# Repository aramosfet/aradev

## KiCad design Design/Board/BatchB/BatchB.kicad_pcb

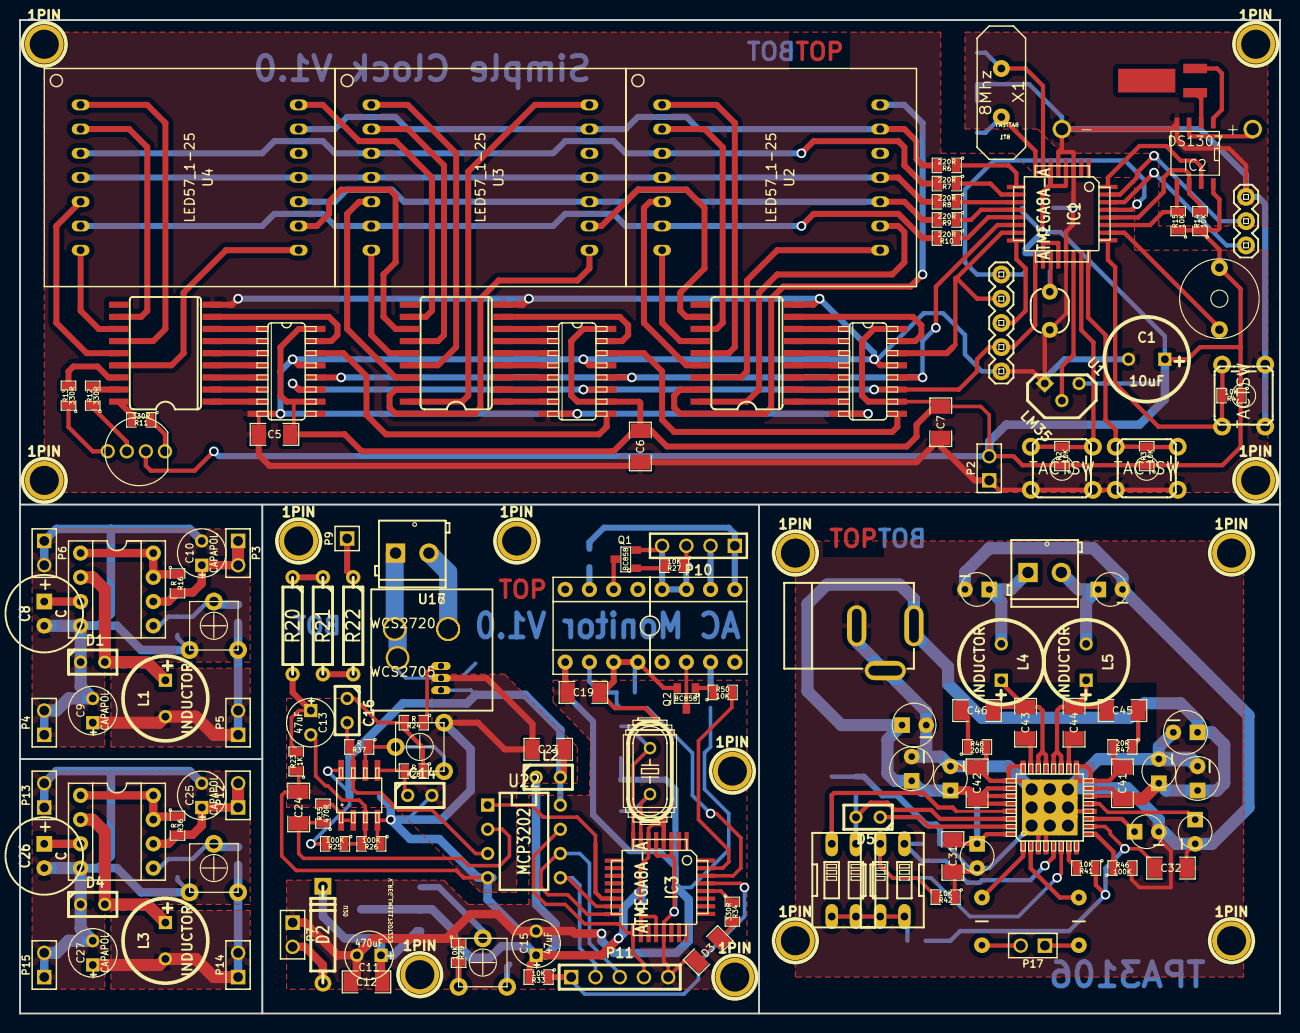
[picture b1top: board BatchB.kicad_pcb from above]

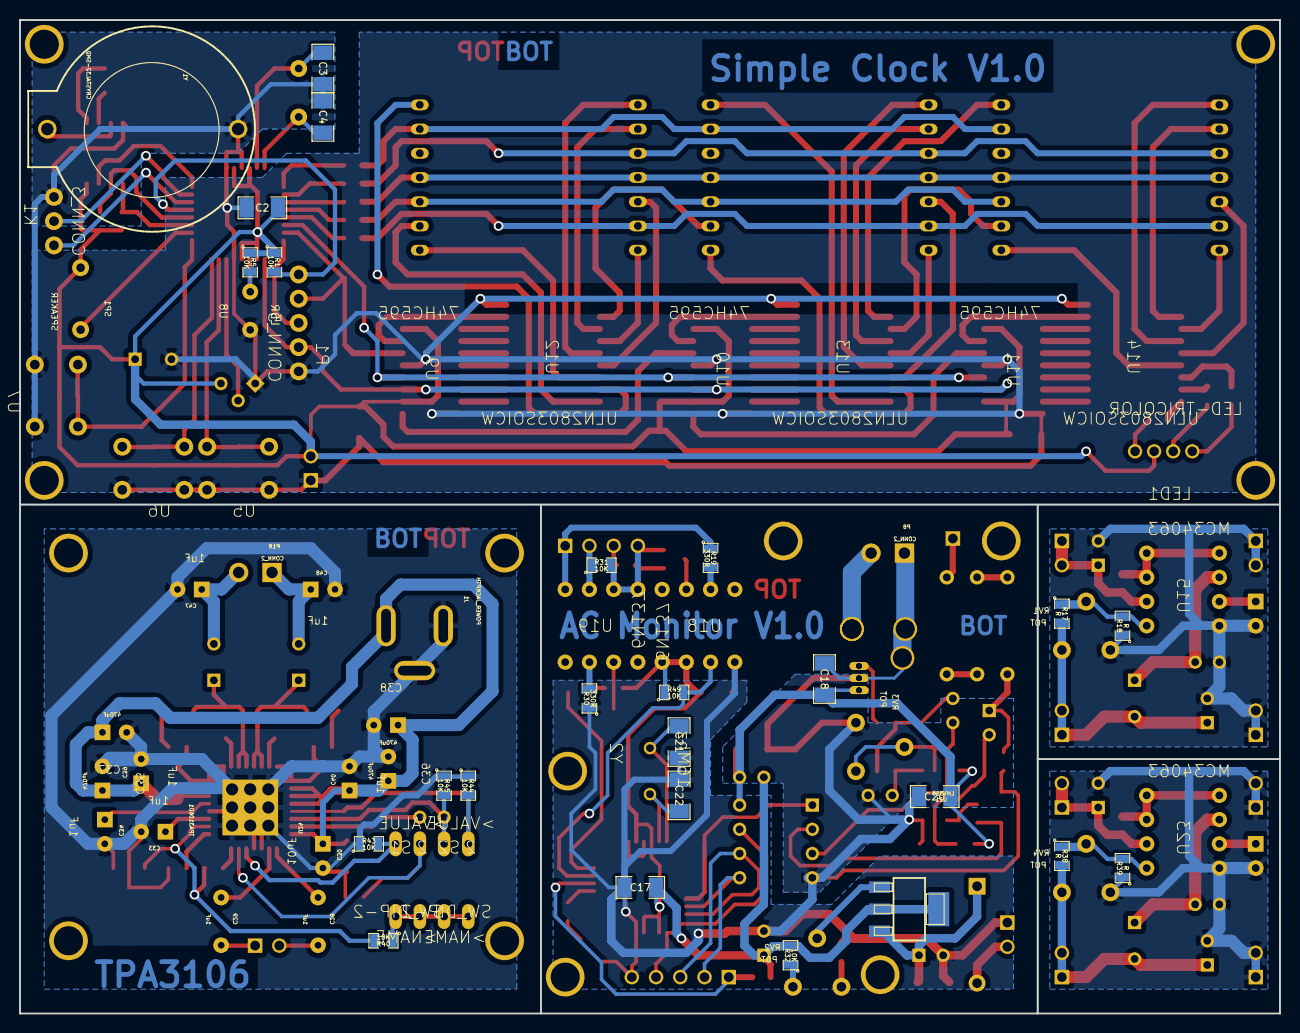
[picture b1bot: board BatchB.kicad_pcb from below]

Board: 4 copper layers, 132.1 x 104.1 mm, 181 parts (25 on the bottom side), 160 nets.

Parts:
1PIN, 1PIN#2, 1PIN#3, 1PIN#4, 1PIN#5, 1PIN#6, 1PIN#7, 1PIN#8, 1PIN#9, 1PIN#10, 1PIN#11, 1PIN#12, 1PIN#13: P***; 1pin
BT1: BATTERY; SparkFun-BATTCOM_20MM_PTH
C1: 10uF; C1.5V8V
C2, C5, C6, C7, C12, C17, C18, C19, C20, C23, C24, C31, C41, C42: 100nF; SM1206
C3, C4: 20pF; SM1206
C8, C26: C; C1V8
C9, C10, C25, C27: CAPAPOL; C1V5
C11: 470uF; C1V5
C13, C15: 47uF; C1V5
C14, C16: C; C1
C21, C22: 22pF; SM1206
C28, C29: 1uF; SparkFun-CAP-PTH-5MM
C30: 10uF; SparkFun-CPOL-RADIAL-10UF-25V
C32: 10nF; SM1206
C33, C34, C39, C40, C47, C48: 1uF; SparkFun-CPOL-RADIAL-10UF-25V
C35, C36, C37, C38: 470uF; SparkFun-CPOL-RADIAL-100UF-25V
C43, C44: 220nF; SM1206
C45, C46: 1nF; SM1206
D1, D4: DIODESCH; C1
D2: 1N4007; D4
D3: LED; SM1206
D5: DIODE; C1
IC1, IC3: ATMEGA8A-A; TQFP32
IC2: DS1307; SO8N
J1: POWER_JACKPTH; SparkFun-POWER_JACK_PTH
K1: CONN_3; SparkFun-1X03
L1, L3, L4, L5: INDUCTOR; C1.5V8V
L2: 100uH; C1
LED1: LED-TRICOLOR; LED-RGB-CA-PTH
P1: CONN_5; SparkFun-1X05
P2, P3, P4, P5, P6, P7, P12, P13, P14, P15, P17: CONN_2; PIN_ARRAY_2X1
P8, P18: CONN_2; SparkFun-SCREWTERMINAL-3.5MM-2
P9: CONN_1; PIN_ARRAY_1
P10: CONN_4; PIN_ARRAY_4x1
P11: CONN_5; PIN_ARRAY_5x1
Q1, Q2: BC858; SOT23
R1, R2, R3, R4, R5, R14, R15, R27, R29, R31, R32, R33, R40, R41, R42, R43, R44, R45, R49, R50: 10K; SM0805
R6, R7, R8, R9, R10: 220R; SM0805
R11, R12, R13, R19, R30, R34: 330R; SM0805
R16, R17, R18, R24, R28, R36, R37, R38, R39: R; SM0805
R20: 56K; R4
R21, R22: 470K; R4
R23: 1K; SM0805
R25, R26, R46: 100K; SM0805
R35: 470R; SM0805
R47, R48: 20R; SM0805
RV1, RV2, RV3, RV4: POT; SparkFun-TRIM_POT_PTH
S1, S2: SW_DIP-2; SparkFun-DIPSWITCH-02
SP1: SPEAKER; SparkFun-BUZZER-12MM
U1: LM35; TO92-123
U2, U3, U4: LED57_1-25
U5, U6, U7: TACTSW; SparkFun-TACTILE-PTH
U8: LDR; SparkFun-PHOTOCELL
U9, U10, U11: 74HC595; SparkFun-SO16
U12, U13, U14: ULN2803SOICW; SparkFun-SO18L
U15, U23: MC34063; SparkFun-DIL08
U16: WCS2705
U17: WCS2720
U18, U19: 6N137; SparkFun-DIL08
U20: V_REG_LM1117SOT223; SparkFun-SOT223
U21: LMV358; SparkFun-SOIC8
U22: MCP3202; DIP-8__300
U24: TPA3106D1; HLQFP33-PowerPAD
X1: 8Mhz; HC-18UV
Y1: CRYSTAL32-SMD; SparkFun-CRYSTAL-32KHZ-SMD
Y2: 16Mhz; SparkFun-HC49U-V

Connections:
/ClassDAmp/GAIN0: R43.2, S1.1, U24.5
/ClassDAmp/GAIN1: R42.2, S1.2, U24.6
/ClassDAmp/MUTE: D5.2, R45.2, S2.1, U24.30
/ClassDAmp/PVCC: C30.1, C31.1, C35.1, C36.1, C37.1, C38.1, C39.1, C40.1, C41.1, C42.1, J1.PWR, U24.14, U24.15, U24.26, U24.27, U24.28, U24.32
/ClassDAmp/SDZ: R44.2, S2.2, U24.29
/ClassDAmp/VREG: C32.1, R40.2, R41.1, U24.10
/EnergyADC/CS: IC3.14, U22.1
/EnergyADC/Iac: C16.2, R37.2, U21.7, U22.3
/EnergyADC/LED: IC3.28, R34.1
/EnergyADC/MISO: IC3.16, P11.3, U22.6
/EnergyADC/MOSI: IC3.15, P11.2, U22.5
/EnergyADC/RXD: IC3.30, R49.2, U18.6
/EnergyADC/Rst: IC3.29, P11.1, R33.1
/EnergyADC/SCK: IC3.17, P11.4, U22.7
/EnergyADC/TXD: IC3.31, R50.2
/EnergyADC/VCCA: C18.2, C20.2, C23.1, L2.2, R25.2, U16.Vdd, U17.Vdd, U21.8, U22.8
/EnergyADC/Vac: C24.2, R35.1, U22.2
/SimpleClock/Bt0: IC1.23, R2.2, U5.3, U5.4
/SimpleClock/Bt1: IC1.24, R3.2, U6.3, U6.4
/SimpleClock/Bt2: IC1.25, R4.2, U7.3, U7.4
/SimpleClock/Buz: IC1.26, SP1.2
/SimpleClock/CS: IC1.14, U9.12, U10.12, U11.12
/SimpleClock/Dc1: R6.2, U2.13, U3.13, U4.13
/SimpleClock/Dc2: R7.2, U2.3, U3.3, U4.3
/SimpleClock/Dc3: R8.2, U2.4, U2.11, U3.4, U3.11, U4.4, U4.11
/SimpleClock/Dc4: R9.2, U2.10, U3.10, U4.10
/SimpleClock/Dc5: R10.2, U2.6, U3.6, U4.6
/SimpleClock/Dr11: U2.9, U12.18
/SimpleClock/Dr12: U2.14, U12.17
/SimpleClock/Dr13: U2.8, U12.16
/SimpleClock/Dr14: U2.5, U12.15
/SimpleClock/Dr15: U2.1, U12.14
/SimpleClock/Dr16: U2.7, U12.13
/SimpleClock/Dr17: U2.2, U12.12
/SimpleClock/Dr21: U3.9, U12.11
/SimpleClock/Dr22: U3.14, U13.18
/SimpleClock/Dr23: U3.8, U13.17
/SimpleClock/Dr24: U3.5, U13.16
/SimpleClock/Dr25: U3.1, U13.15
/SimpleClock/Dr26: U3.7, U13.14
/SimpleClock/Dr27: U3.2, U13.13
/SimpleClock/Dr31: U4.9, U13.12
/SimpleClock/Dr32: U4.14, U13.11
/SimpleClock/Dr33: U4.8, U14.15
/SimpleClock/Dr34: U4.5, U14.14
/SimpleClock/Dr35: U4.1, U14.13
/SimpleClock/Dr36: U4.7, U14.12
/SimpleClock/Dr37: U4.2, U14.11
/SimpleClock/INT: IC1.32, IC2.7
/SimpleClock/LDR: IC1.19, R5.2, U8.1
/SimpleClock/LEDB: R13.2, U14.16
/SimpleClock/LEDG: R12.2, U14.17
/SimpleClock/LEDR: R11.2, U14.18
/SimpleClock/MISO: IC1.16, P1.3
/SimpleClock/MOSI: IC1.15, P1.4, U9.14
/SimpleClock/Qb1: U9.7, U12.1
/SimpleClock/Qb2: U9.6, U12.2
/SimpleClock/Qb3: U9.5, U12.3
/SimpleClock/Qb4: U9.4, U12.4
/SimpleClock/Qb5: U9.3, U12.5
/SimpleClock/Qb6: U9.2, U12.6
/SimpleClock/Qb7: U9.1, U12.7
/SimpleClock/Qb8: U9.15, U12.8
/SimpleClock/Qb9: U10.7, U13.1
/SimpleClock/Qb10: U10.6, U13.2
/SimpleClock/Qb11: U10.5, U13.3
/SimpleClock/Qb12: U10.4, U13.4
/SimpleClock/Qb13: U10.3, U13.5
/SimpleClock/Qb14: U10.2, U13.6
/SimpleClock/Qb15: U10.1, U13.7
/SimpleClock/Qb16: U10.15, U13.8
/SimpleClock/Qb17: U11.7, U14.1
/SimpleClock/Qb18: U11.6, U14.2
/SimpleClock/Qb19: U11.5, U14.3
/SimpleClock/Qb20: U11.4, U14.4
/SimpleClock/Qb21: U11.3, U14.5
/SimpleClock/Qb22: U11.2, U14.6
/SimpleClock/Qb23: U11.1, U14.7
/SimpleClock/Qb24: U11.15, U14.8
/SimpleClock/RST: IC1.29, P1.5, R1.2
/SimpleClock/RXD: IC1.30, K1.3
/SimpleClock/SCK: IC1.17, P1.2, U9.11, U10.11, U11.11
/SimpleClock/SCL: IC1.28, IC2.6, R14.2
/SimpleClock/SDA: IC1.27, IC2.5, R15.2
/SimpleClock/TXD: IC1.31, K1.2
/SimpleClock/Temp: IC1.22, U1.2
GND: BT1.2, C1.2, C2.2, C3.2, C4.2, C5.2, C6.2, C7.2, C8.2, C9.2, C10.2, C11.2, C12.1, C14.2, C15.2, C17.1, C18.1, C19.1, C20.1, C21.1, C22.1, C23.2, C24.1, C25.2, C26.2, C27.2, C30.2, C31.2, C32.2, C33.2, C34.2, C35.2, C36.2, C37.2, C38.2, C39.2, C40.2, C41.2, C42.2, C47.2, C48.2, D1.1, D3.2, D4.1, IC1.3, IC1.5, IC1.21, IC2.4, IC3.3, IC3.5, IC3.21, J1.GND, J1.GNDB, K1.1, P1.1, P2.1, P4.1, P4.2, P6.1, P6.2, P7.1, P8.1, P11.5, P13.1, P13.2, P15.1, P15.2, R18.1, R23.1, R26.1, R29.1, R30.1, R39.1, R42.1, R43.1, R44.1, R45.1, R46.2, R47.2, R48.2, RV1.1, RV3.3, RV4.1, U1.3, U5.1, U5.2, U6.1, U6.2, U7.1, U7.2, U8.2, U9.8, U9.13, U10.8, U10.13, U11.8, U11.13, U12.9, U13.9, U14.9, U15.4, U16.Gnd, U16.IP-, U17.Gnd, U17.IP-, U18.5, U21.4, U22.4, U23.4, U24.3, U24.4, U24.12, U24.16, U24.17, U24.24, U24.25, U24.33
unnamed: IC1.9, R6.1
unnamed: IC1.11, R8.1
unnamed: IC1.12, R9.1
unnamed: IC1.13, R10.1
unnamed: IC1.10, R7.1
unnamed: BT1.1, IC2.3
unnamed: IC2.1, Y1.2
unnamed: IC2.2, Y1.1
unnamed: LED1.B, R12.1
unnamed: LED1.G, R13.1
unnamed: LED1.R, R11.1
unnamed: C3.1, IC1.7, X1.1
unnamed: C4.1, IC1.8, X1.2
unnamed: U10.9, U11.14
unnamed: U9.9, U10.14
unnamed: C26.1, U23.3
unnamed: R36.1, U23.1, U23.7, U23.8
unnamed: D4.2, L3.1, U23.2
unnamed: C27.1, L3.2, P14.1, P14.2, R38.2, RV4.3
unnamed: R38.1, R39.2, RV4.2, U23.5
unnamed: C8.1, U15.3
unnamed: R16.1, U15.1, U15.7, U15.8
unnamed: D1.2, L1.1, U15.2
unnamed: C9.1, L1.2, P5.1, P5.2, R17.2, RV1.3
unnamed: R17.1, R18.2, RV1.2, U15.5
unnamed: D2.1, P7.2
unnamed: C14.1, R28.2, U21.5
unnamed: R35.2, U21.1, U21.2
unnamed: R32.1, RV2.3
unnamed: R29.2, RV2.1
unnamed: RV2.2, U20.1
unnamed: C11.1, C12.2, D2.2, U20.3
unnamed: C16.1, R24.2, R28.1
unnamed: P10.3, R27.1
unnamed: Q1.1, R27.2
unnamed: Q2.1, R50.1
unnamed: R30.2, U19.3
unnamed: Q1.3, U18.2
unnamed: R19.2, U18.3
unnamed: P9.1, R22.1
unnamed: C21.2, IC3.8, Y2.1
unnamed: R37.1, RV3.1, RV3.2, U21.6
unnamed: Q2.3, U19.2
unnamed: P10.1, R19.1, U19.5
unnamed: P10.2, R31.1, U19.6
unnamed: C13.2, R25.1, R26.2, U21.3
unnamed: C13.1, R20.2, R23.2
unnamed: R20.1, R21.1
unnamed: R21.2, R22.2
unnamed: C22.2, IC3.7, Y2.2
unnamed: P8.2, U16.IP+, U17.IP+
unnamed: R24.1, U16.Vo, U17.Vo
unnamed: D3.1, R34.2
unnamed: P10.4, Q1.2, R31.2, U19.7, U19.8
unnamed: C29.1, P17.1
unnamed: C28.1, P17.2
unnamed: D5.1, U24.31
unnamed: C29.2, U24.2
unnamed: C28.2, U24.1
unnamed: C46.1, R48.1
unnamed: C45.1, R47.1
unnamed: R40.1, S1.3, S1.4, S2.3, S2.4
unnamed: C43.2, C46.2, L4.1, U24.21, U24.22
unnamed: C44.1, U24.18
unnamed: C43.1, U24.23
unnamed: R46.1, U24.9
unnamed: C33.1, U24.11
unnamed: C44.2, C45.2, L5.1, U24.19, U24.20
unnamed: C47.1, L5.2, P18.2
unnamed: C48.1, L4.2, P18.1
unnamed: R41.2, U24.7
unnamed: C34.1, U24.13
VCC: C1.1, C2.1, C5.1, C6.1, C7.1, C10.1, C15.1, C17.2, C19.2, C25.1, IC1.4, IC1.6, IC1.18, IC1.20, IC2.8, IC3.4, IC3.6, IC3.18, IC3.20, L2.1, LED1.A, P2.2, P3.1, P3.2, P12.1, P12.2, Q2.2, R1.1, R2.1, R3.1, R4.1, R5.1, R14.1, R15.1, R16.2, R32.2, R33.2, R36.2, R49.1, SP1.1, U1.1, U9.10, U9.16, U10.10, U10.16, U11.10, U11.16, U15.6, U18.7, U18.8, U20.2, U20.4, U23.6

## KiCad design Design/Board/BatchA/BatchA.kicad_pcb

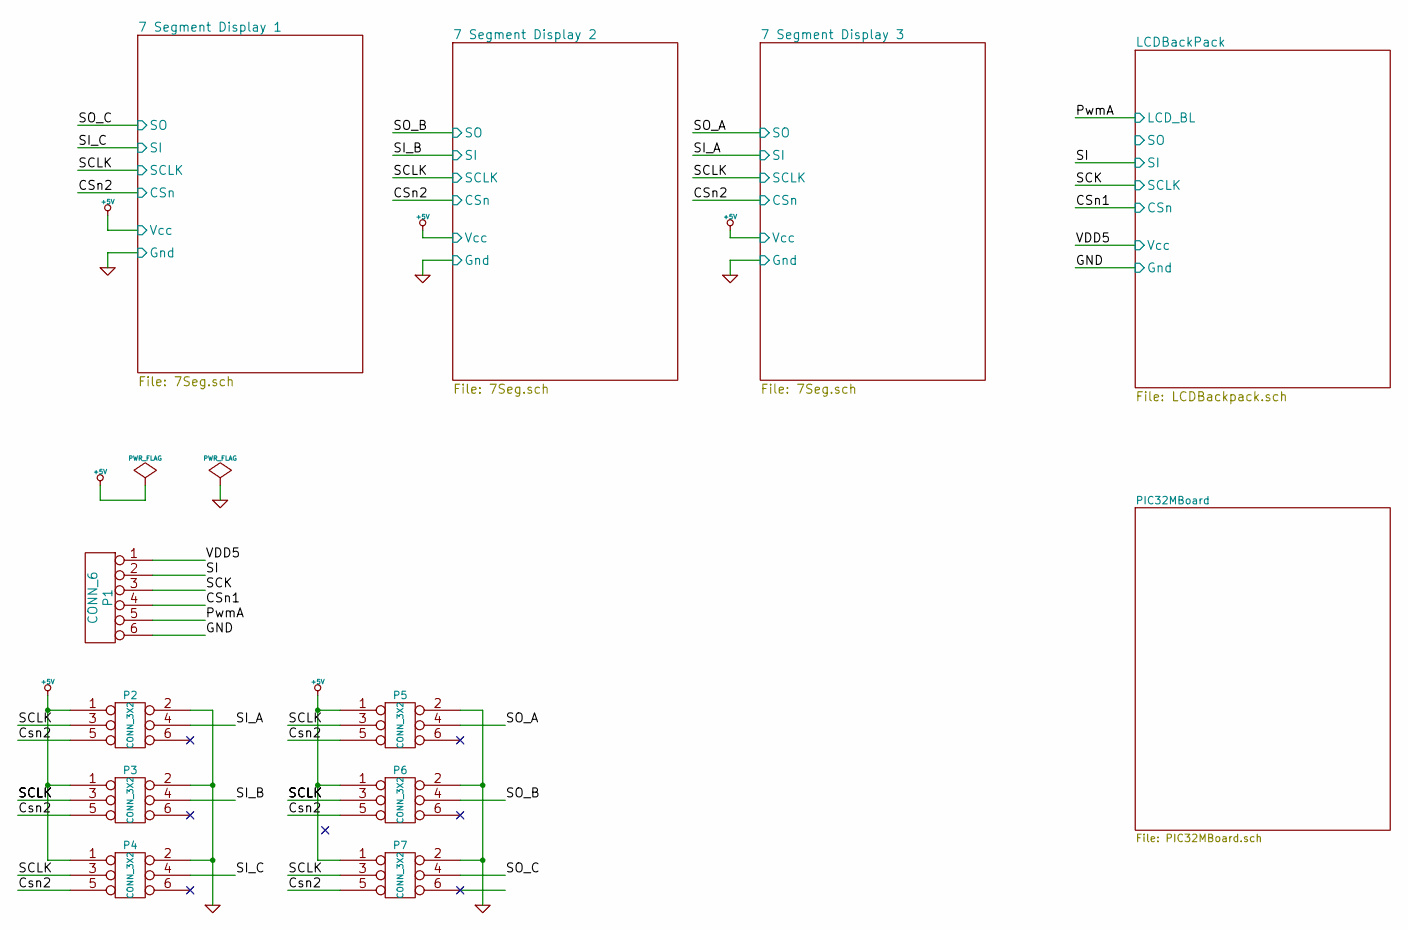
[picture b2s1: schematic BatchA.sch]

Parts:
P1: CONN_6
P2, P3, P4, P5, P6, P7: CONN_3X2

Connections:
+5V: P1.1, P2.1, P3.1, P4.1, P5.1, P6.1, P7.1; also elsewhere on the board
/7 Segment Display 1/CSn: P2.5, P3.5, P4.5, P5.5, P6.5, P7.5; also elsewhere on the board
/7 Segment Display 1/SCLK: P2.3, P3.3, P4.3, P5.3, P6.3, P7.3; also elsewhere on the board
/7 Segment Display 1/SI: P4.4; also elsewhere on the board
/7 Segment Display 1/SO: P7.4; also elsewhere on the board
/7 Segment Display 2/SI: P3.4; also elsewhere on the board
/7 Segment Display 2/SO: P6.4; also elsewhere on the board
/7 Segment Display 3/SI: P2.4; also elsewhere on the board
/7 Segment Display 3/SO: P5.4; also elsewhere on the board
/LCDBackPack/CSn: P1.4; also elsewhere on the board
/LCDBackPack/LCD_BL: P1.5; also elsewhere on the board
/LCDBackPack/SCLK: P1.3; also elsewhere on the board
/LCDBackPack/SI: P1.2; also elsewhere on the board
GND: P1.6, P2.2, P3.2, P4.2, P5.2, P6.2, P7.2; also elsewhere on the board

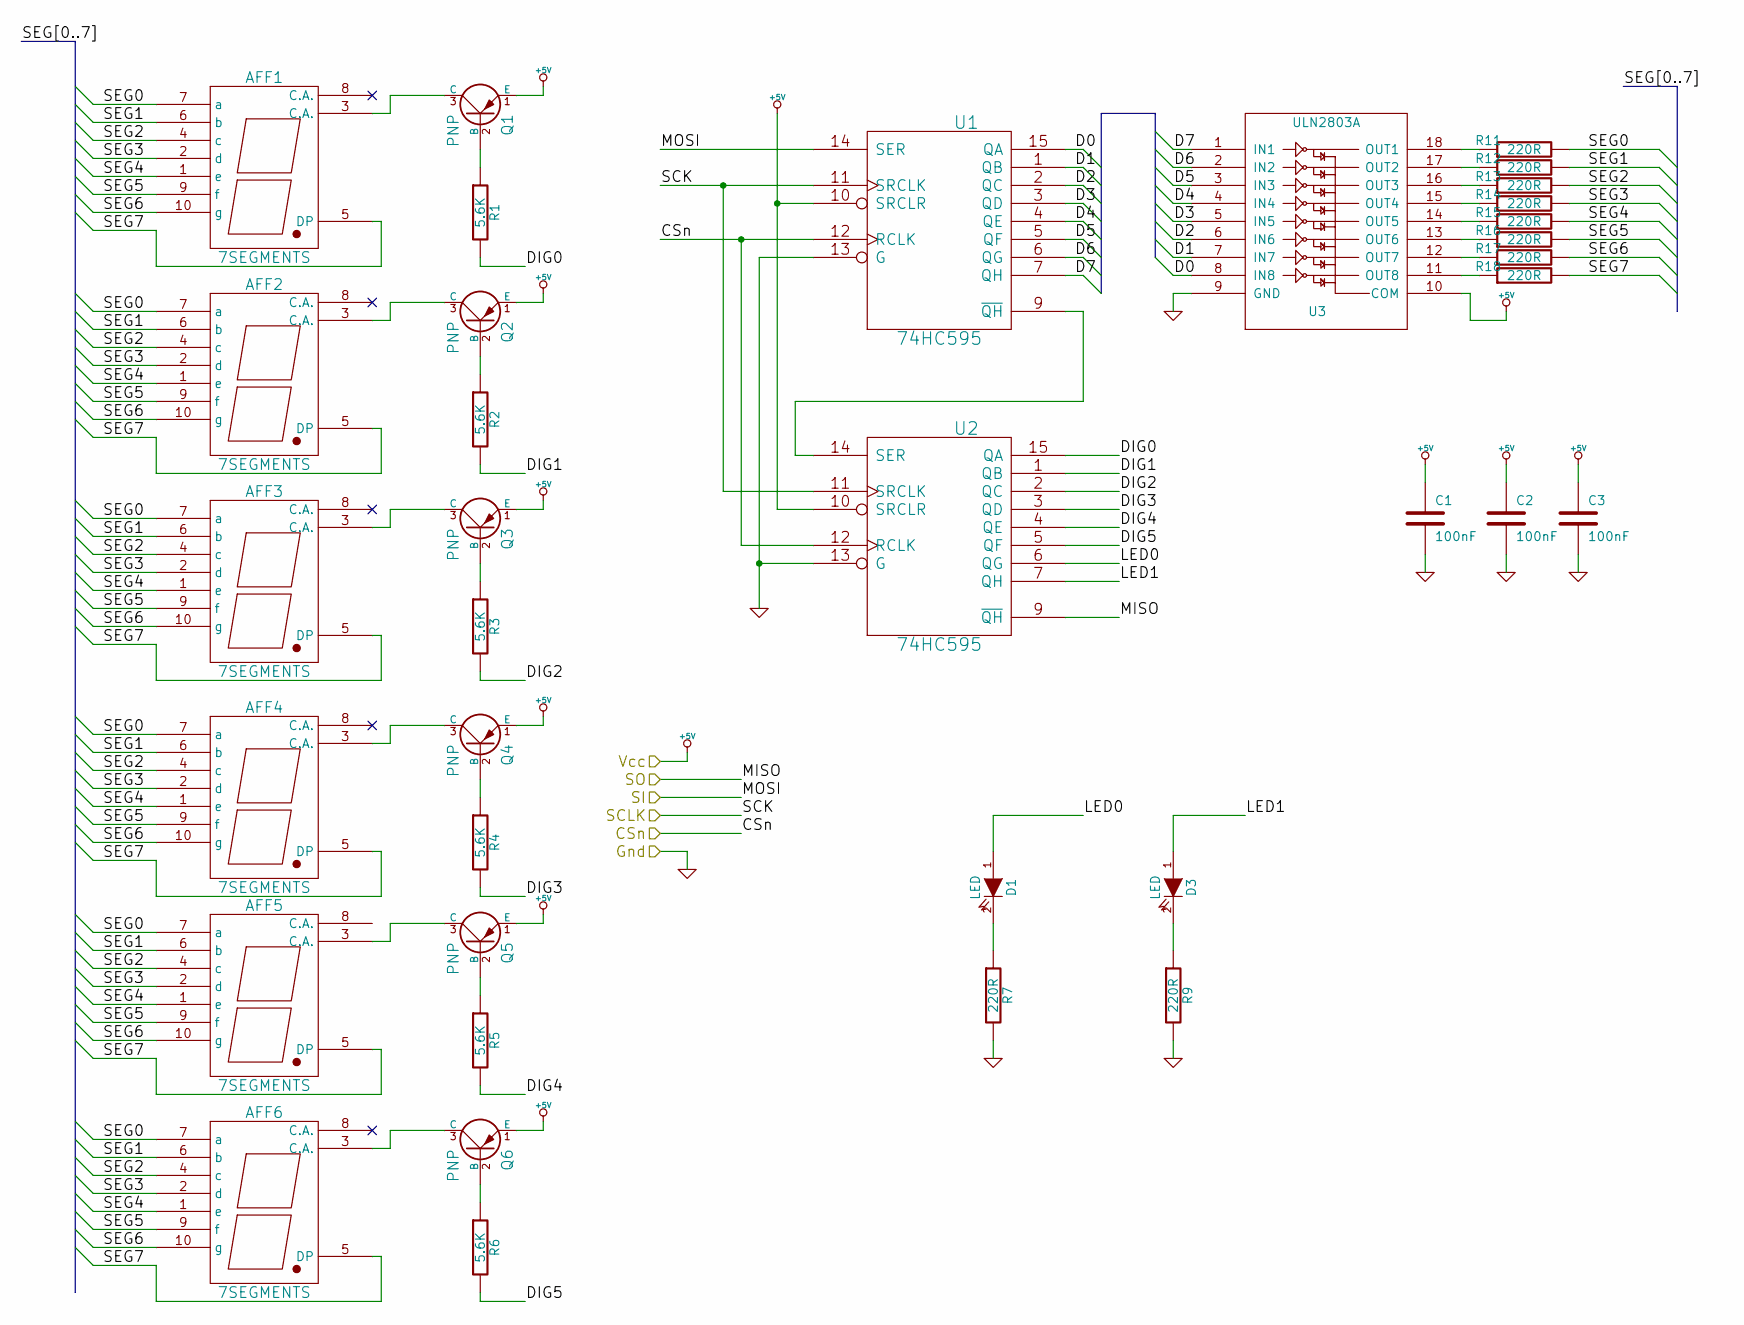
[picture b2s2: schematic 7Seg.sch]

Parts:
AFF13, AFF14, AFF15, AFF16, AFF17, AFF18: 7SEGMENTS
C9, C10, C11: 100nF
D9, D11: LED
Q13, Q14, Q15, Q16, Q17, Q18: PNP
R37, R38, R39, R40, R41, R42: 5.6K
R43, R45, R47, R48, R49, R50, R51, R52, R53, R54: 220R
U7, U8: 74HC595
U9: ULN2803A

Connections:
+5V: C9.1, C10.1, C11.1, Q13.1 (E), Q14.1 (E), Q15.1 (E), Q16.1 (E), Q17.1 (E), Q18.1 (E), U7.10 (SRCLR), U7.16 (VCC), U8.10 (SRCLR), U8.16 (VCC), U9.10 (COM); also elsewhere on the board
/7 Segment Display 1/CSn: U7.12 (RCLK), U8.12 (RCLK); also elsewhere on the board
/7 Segment Display 1/D0: U7.15 (QA), U9.8 (IN8)
/7 Segment Display 1/D1: U7.1 (QB), U9.7 (IN7)
/7 Segment Display 1/D2: U7.2 (QC), U9.6 (IN6)
/7 Segment Display 1/D3: U7.3 (QD), U9.5 (IN5)
/7 Segment Display 1/D4: U7.4 (QE), U9.4 (IN4)
/7 Segment Display 1/D5: U7.5 (QF), U9.3 (IN3)
/7 Segment Display 1/D6: U7.6 (QG), U9.2 (IN2)
/7 Segment Display 1/D7: U7.7 (QH), U9.1 (IN1)
/7 Segment Display 1/DIG0: R37.2, U8.15 (QA)
/7 Segment Display 1/DIG1: R38.2, U8.1 (QB)
/7 Segment Display 1/DIG2: R39.2, U8.2 (QC)
/7 Segment Display 1/DIG3: R40.2, U8.3 (QD)
/7 Segment Display 1/DIG4: R41.2, U8.4 (QE)
/7 Segment Display 1/DIG5: R42.2, U8.5 (QF)
/7 Segment Display 1/LED0: D9.1 (A), U8.6 (QG)
/7 Segment Display 1/LED1: D11.1 (A), U8.7 (QH)
/7 Segment Display 1/SCLK: U7.11 (SRCLK), U8.11 (SRCLK); also elsewhere on the board
/7 Segment Display 1/SEG0: AFF13.7 (a), AFF14.7 (a), AFF15.7 (a), AFF16.7 (a), AFF17.7 (a), AFF18.7 (a), R47.2
/7 Segment Display 1/SEG1: AFF13.6 (b), AFF14.6 (b), AFF15.6 (b), AFF16.6 (b), AFF17.6 (b), AFF18.6 (b), R48.2
/7 Segment Display 1/SEG2: AFF13.4 (c), AFF14.4 (c), AFF15.4 (c), AFF16.4 (c), AFF17.4 (c), AFF18.4 (c), R49.2
/7 Segment Display 1/SEG3: AFF13.2 (d), AFF14.2 (d), AFF15.2 (d), AFF16.2 (d), AFF17.2 (d), AFF18.2 (d), R50.2
/7 Segment Display 1/SEG4: AFF13.1 (e), AFF14.1 (e), AFF15.1 (e), AFF16.1 (e), AFF17.1 (e), AFF18.1 (e), R51.2
/7 Segment Display 1/SEG5: AFF13.9 (f), AFF14.9 (f), AFF15.9 (f), AFF16.9 (f), AFF17.9 (f), AFF18.9 (f), R52.2
/7 Segment Display 1/SEG6: AFF13.10 (g), AFF14.10 (g), AFF15.10 (g), AFF16.10 (g), AFF17.10 (g), AFF18.10 (g), R53.2
/7 Segment Display 1/SEG7: AFF13.5 (DP), AFF14.5 (DP), AFF15.5 (DP), AFF16.5 (DP), AFF17.5 (DP), AFF18.5 (DP), R54.2
/7 Segment Display 1/SI: U7.14 (SER); also elsewhere on the board
/7 Segment Display 1/SO: U8.9 (~QH); also elsewhere on the board
GND: C9.2, C10.2, C11.2, R43.2, R45.2, U7.8 (GND), U7.13 (G), U8.8 (GND), U8.13 (G), U9.9 (GND); also elsewhere on the board
unnamed: Q16.2 (B), R40.1
unnamed: AFF14.3 (C.A.), Q14.3 (C)
unnamed: AFF15.3 (C.A.), Q15.3 (C)
unnamed: Q15.2 (B), R39.1
unnamed: Q18.2 (B), R42.1
unnamed: AFF16.3 (C.A.), Q16.3 (C)
unnamed: AFF17.3 (C.A.), Q17.3 (C)
unnamed: Q17.2 (B), R41.1
unnamed: R47.1, U9.18 (OUT1)
unnamed: R48.1, U9.17 (OUT2)
unnamed: Q14.2 (B), R38.1
unnamed: R49.1, U9.16 (OUT3)
unnamed: R50.1, U9.15 (OUT4)
unnamed: R51.1, U9.14 (OUT5)
unnamed: R52.1, U9.13 (OUT6)
unnamed: AFF18.3 (C.A.), Q18.3 (C)
unnamed: R53.1, U9.12 (OUT7)
unnamed: R54.1, U9.11 (OUT8)
unnamed: Q13.2 (B), R37.1
unnamed: D9.2 (K), R43.1
unnamed: D11.2 (K), R45.1
unnamed: AFF13.3 (C.A.), Q13.3 (C)
unnamed: U7.9 (~QH), U8.14 (SER)

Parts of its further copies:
AFF1, AFF2, AFF3, AFF4, AFF5, AFF6, AFF7, AFF8, AFF9, AFF10, AFF11, AFF12: 7SEGMENTS
C1, C2, C3, C5, C6, C7: 100nF
D1, D3, D5, D7: LED
Q1, Q2, Q3, Q4, Q5, Q6, Q7, Q8, Q9, Q10, Q11, Q12: PNP
R1, R2, R3, R4, R5, R6, R19, R20, R21, R22, R23, R24: 5.6K
R7, R9, R11, R12, R13, R14, R15, R16, R17, R18, R25, R27, R29, R30, R31, R32, R33, R34, R35, R36: 220R
U1, U2, U4, U5: 74HC595
U3, U6: ULN2803A

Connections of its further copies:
+5V: C1.1, C2.1, C3.1, C5.1, C6.1, C7.1, Q1.1 (E), Q2.1 (E), Q3.1 (E), Q4.1 (E), Q5.1 (E), Q6.1 (E), Q7.1 (E), Q8.1 (E), Q9.1 (E), Q10.1 (E), Q11.1 (E), Q12.1 (E), U1.10 (SRCLR), U1.16 (VCC), U2.10 (SRCLR), U2.16 (VCC), U3.10 (COM), U4.10 (SRCLR), U4.16 (VCC), U5.10 (SRCLR), U5.16 (VCC), U6.10 (COM); also elsewhere on the board
/7 Segment Display 1/CSn: U1.12 (RCLK), U2.12 (RCLK), U4.12 (RCLK), U5.12 (RCLK); also elsewhere on the board
/7 Segment Display 1/SCLK: U1.11 (SRCLK), U2.11 (SRCLK), U4.11 (SRCLK), U5.11 (SRCLK); also elsewhere on the board
/7 Segment Display 2/D0: U4.15 (QA), U6.8 (IN8)
/7 Segment Display 2/D1: U4.1 (QB), U6.7 (IN7)
/7 Segment Display 2/D2: U4.2 (QC), U6.6 (IN6)
/7 Segment Display 2/D3: U4.3 (QD), U6.5 (IN5)
/7 Segment Display 2/D4: U4.4 (QE), U6.4 (IN4)
/7 Segment Display 2/D5: U4.5 (QF), U6.3 (IN3)
/7 Segment Display 2/D6: U4.6 (QG), U6.2 (IN2)
/7 Segment Display 2/D7: U4.7 (QH), U6.1 (IN1)
/7 Segment Display 2/DIG0: R19.2, U5.15 (QA)
/7 Segment Display 2/DIG1: R20.2, U5.1 (QB)
/7 Segment Display 2/DIG2: R21.2, U5.2 (QC)
/7 Segment Display 2/DIG3: R22.2, U5.3 (QD)
/7 Segment Display 2/DIG4: R23.2, U5.4 (QE)
/7 Segment Display 2/DIG5: R24.2, U5.5 (QF)
/7 Segment Display 2/LED0: D5.1 (A), U5.6 (QG)
/7 Segment Display 2/LED1: D7.1 (A), U5.7 (QH)
/7 Segment Display 2/SEG0: AFF7.7 (a), AFF8.7 (a), AFF9.7 (a), AFF10.7 (a), AFF11.7 (a), AFF12.7 (a), R29.2
/7 Segment Display 2/SEG1: AFF7.6 (b), AFF8.6 (b), AFF9.6 (b), AFF10.6 (b), AFF11.6 (b), AFF12.6 (b), R30.2
/7 Segment Display 2/SEG2: AFF7.4 (c), AFF8.4 (c), AFF9.4 (c), AFF10.4 (c), AFF11.4 (c), AFF12.4 (c), R31.2
/7 Segment Display 2/SEG3: AFF7.2 (d), AFF8.2 (d), AFF9.2 (d), AFF10.2 (d), AFF11.2 (d), AFF12.2 (d), R32.2
/7 Segment Display 2/SEG4: AFF7.1 (e), AFF8.1 (e), AFF9.1 (e), AFF10.1 (e), AFF11.1 (e), AFF12.1 (e), R33.2
/7 Segment Display 2/SEG5: AFF7.9 (f), AFF8.9 (f), AFF9.9 (f), AFF10.9 (f), AFF11.9 (f), AFF12.9 (f), R34.2
/7 Segment Display 2/SEG6: AFF7.10 (g), AFF8.10 (g), AFF9.10 (g), AFF10.10 (g), AFF11.10 (g), AFF12.10 (g), R35.2
/7 Segment Display 2/SEG7: AFF7.5 (DP), AFF8.5 (DP), AFF9.5 (DP), AFF10.5 (DP), AFF11.5 (DP), AFF12.5 (DP), R36.2
/7 Segment Display 2/SI: U4.14 (SER); also elsewhere on the board
/7 Segment Display 2/SO: U5.9 (~QH); also elsewhere on the board
/7 Segment Display 3/D0: U1.15 (QA), U3.8 (IN8)
/7 Segment Display 3/D1: U1.1 (QB), U3.7 (IN7)
/7 Segment Display 3/D2: U1.2 (QC), U3.6 (IN6)
/7 Segment Display 3/D3: U1.3 (QD), U3.5 (IN5)
/7 Segment Display 3/D4: U1.4 (QE), U3.4 (IN4)
/7 Segment Display 3/D5: U1.5 (QF), U3.3 (IN3)
/7 Segment Display 3/D6: U1.6 (QG), U3.2 (IN2)
/7 Segment Display 3/D7: U1.7 (QH), U3.1 (IN1)
/7 Segment Display 3/DIG0: R1.2, U2.15 (QA)
/7 Segment Display 3/DIG1: R2.2, U2.1 (QB)
/7 Segment Display 3/DIG2: R3.2, U2.2 (QC)
/7 Segment Display 3/DIG3: R4.2, U2.3 (QD)
/7 Segment Display 3/DIG4: R5.2, U2.4 (QE)
/7 Segment Display 3/DIG5: R6.2, U2.5 (QF)
/7 Segment Display 3/LED0: D1.1 (A), U2.6 (QG)
/7 Segment Display 3/LED1: D3.1 (A), U2.7 (QH)
/7 Segment Display 3/SEG0: AFF1.7 (a), AFF2.7 (a), AFF3.7 (a), AFF4.7 (a), AFF5.7 (a), AFF6.7 (a), R11.2
/7 Segment Display 3/SEG1: AFF1.6 (b), AFF2.6 (b), AFF3.6 (b), AFF4.6 (b), AFF5.6 (b), AFF6.6 (b), R12.2
/7 Segment Display 3/SEG2: AFF1.4 (c), AFF2.4 (c), AFF3.4 (c), AFF4.4 (c), AFF5.4 (c), AFF6.4 (c), R13.2
/7 Segment Display 3/SEG3: AFF1.2 (d), AFF2.2 (d), AFF3.2 (d), AFF4.2 (d), AFF5.2 (d), AFF6.2 (d), R14.2
/7 Segment Display 3/SEG4: AFF1.1 (e), AFF2.1 (e), AFF3.1 (e), AFF4.1 (e), AFF5.1 (e), AFF6.1 (e), R15.2
/7 Segment Display 3/SEG5: AFF1.9 (f), AFF2.9 (f), AFF3.9 (f), AFF4.9 (f), AFF5.9 (f), AFF6.9 (f), R16.2
/7 Segment Display 3/SEG6: AFF1.10 (g), AFF2.10 (g), AFF3.10 (g), AFF4.10 (g), AFF5.10 (g), AFF6.10 (g), R17.2
/7 Segment Display 3/SEG7: AFF1.5 (DP), AFF2.5 (DP), AFF3.5 (DP), AFF4.5 (DP), AFF5.5 (DP), AFF6.5 (DP), R18.2
/7 Segment Display 3/SI: U1.14 (SER); also elsewhere on the board
/7 Segment Display 3/SO: U2.9 (~QH); also elsewhere on the board
GND: C1.2, C2.2, C3.2, C5.2, C6.2, C7.2, R7.2, R9.2, R25.2, R27.2, U1.8 (GND), U1.13 (G), U2.8 (GND), U2.13 (G), U3.9 (GND), U4.8 (GND), U4.13 (G), U5.8 (GND), U5.13 (G), U6.9 (GND); also elsewhere on the board
unnamed: R30.1, U6.17 (OUT2)
unnamed: R32.1, U6.15 (OUT4)
unnamed: R34.1, U6.13 (OUT6)
unnamed: R36.1, U6.11 (OUT8)
unnamed: Q7.2 (B), R19.1
unnamed: AFF7.3 (C.A.), Q7.3 (C)
unnamed: R35.1, U6.12 (OUT7)
unnamed: R33.1, U6.14 (OUT5)
unnamed: R31.1, U6.16 (OUT3)
unnamed: R29.1, U6.18 (OUT1)
unnamed: U4.9 (~QH), U5.14 (SER)
unnamed: AFF10.3 (C.A.), Q10.3 (C)
unnamed: AFF11.3 (C.A.), Q11.3 (C)
unnamed: AFF12.3 (C.A.), Q12.3 (C)
unnamed: D7.2 (K), R27.1
unnamed: D5.2 (K), R25.1
unnamed: Q12.2 (B), R24.1
unnamed: Q11.2 (B), R23.1
unnamed: Q9.2 (B), R21.1
unnamed: AFF9.3 (C.A.), Q9.3 (C)
unnamed: AFF8.3 (C.A.), Q8.3 (C)
unnamed: Q10.2 (B), R22.1
unnamed: Q8.2 (B), R20.1
unnamed: D1.2 (K), R7.1
unnamed: D3.2 (K), R9.1
unnamed: Q2.2 (B), R2.1
unnamed: Q1.2 (B), R1.1
unnamed: AFF3.3 (C.A.), Q3.3 (C)
unnamed: R11.1, U3.18 (OUT1)
unnamed: R12.1, U3.17 (OUT2)
unnamed: R13.1, U3.16 (OUT3)
unnamed: R14.1, U3.15 (OUT4)
unnamed: R15.1, U3.14 (OUT5)
unnamed: R16.1, U3.13 (OUT6)
unnamed: R17.1, U3.12 (OUT7)
unnamed: Q6.2 (B), R6.1
unnamed: Q5.2 (B), R5.1
unnamed: AFF5.3 (C.A.), Q5.3 (C)
unnamed: Q3.2 (B), R3.1
unnamed: Q4.2 (B), R4.1
unnamed: R18.1, U3.11 (OUT8)
unnamed: AFF4.3 (C.A.), Q4.3 (C)
unnamed: AFF2.3 (C.A.), Q2.3 (C)
unnamed: AFF1.3 (C.A.), Q1.3 (C)
unnamed: U1.9 (~QH), U2.14 (SER)
unnamed: AFF6.3 (C.A.), Q6.3 (C)

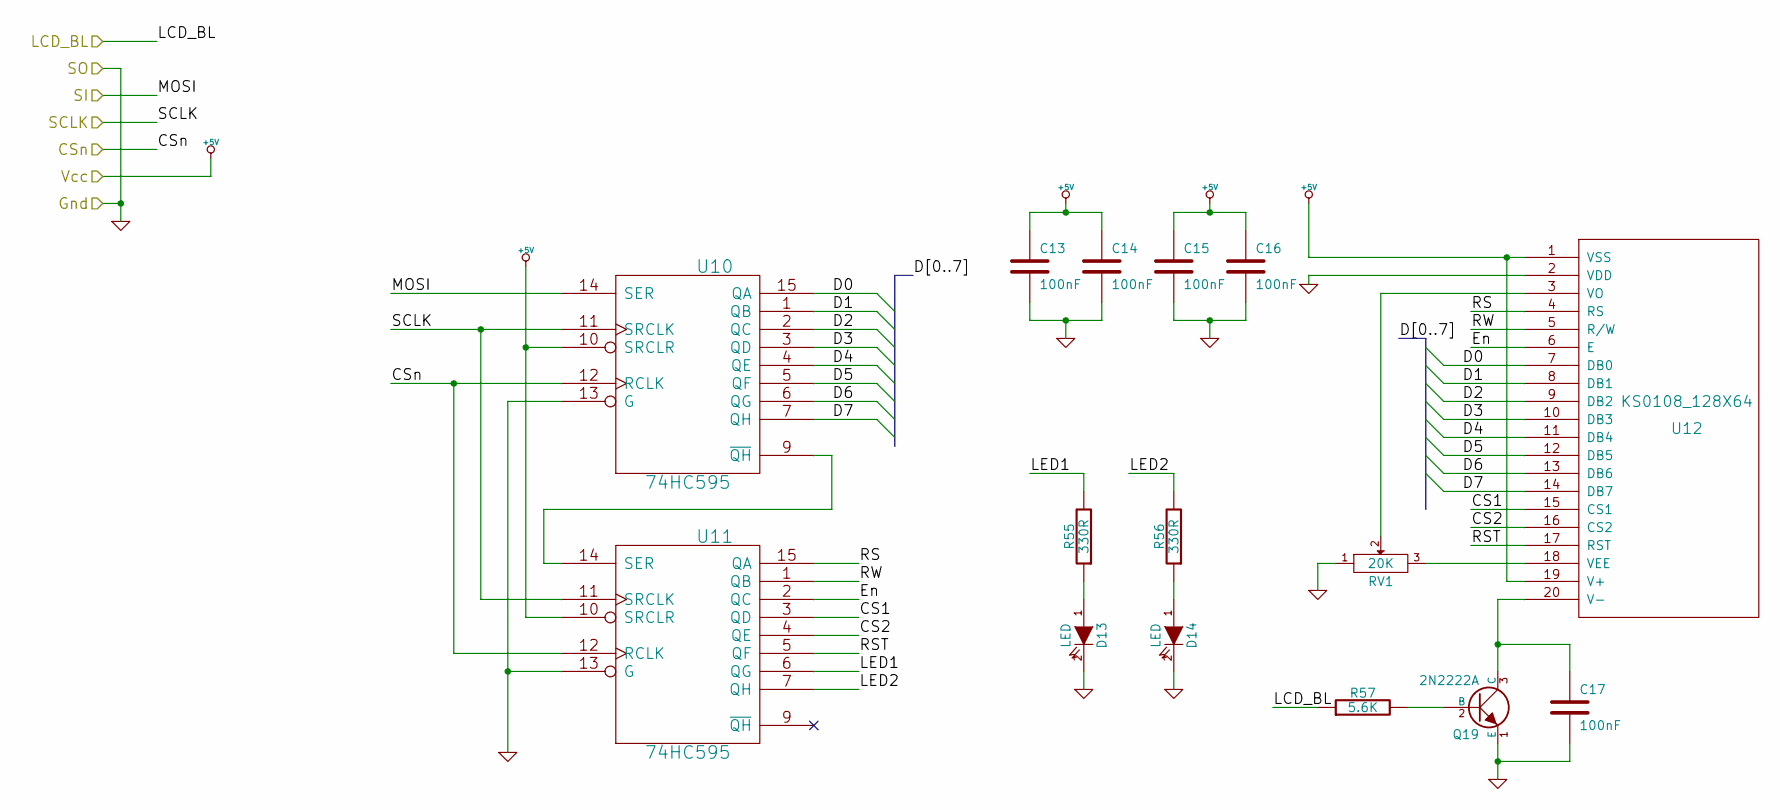
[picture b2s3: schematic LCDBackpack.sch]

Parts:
C13, C14, C15, C16, C17: 100nF
D13, D14: LED
Q19: 2N2222A
R55, R56: 330R
R57: 5.6K
RV1: 20K
U10, U11: 74HC595
U12: KS0108_128X64

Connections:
+5V: C13.1, C14.1, C15.1, C16.1, U10.10 (SRCLR), U10.16 (VCC), U11.10 (SRCLR), U11.16 (VCC), U12.1 (VSS), U12.19 (V+); also elsewhere on the board
/LCDBackPack/CS1: U11.3 (QD), U12.15 (CS1)
/LCDBackPack/CS2: U11.4 (QE), U12.16 (CS2)
/LCDBackPack/CSn: U10.12 (RCLK), U11.12 (RCLK); also elsewhere on the board
/LCDBackPack/D0: U10.15 (QA), U12.7 (DB0)
/LCDBackPack/D1: U10.1 (QB), U12.8 (DB1)
/LCDBackPack/D2: U10.2 (QC), U12.9 (DB2)
/LCDBackPack/D3: U10.3 (QD), U12.10 (DB3)
/LCDBackPack/D4: U10.4 (QE), U12.11 (DB4)
/LCDBackPack/D5: U10.5 (QF), U12.12 (DB5)
/LCDBackPack/D6: U10.6 (QG), U12.13 (DB6)
/LCDBackPack/D7: U10.7 (QH), U12.14 (DB7)
/LCDBackPack/En: U11.2 (QC), U12.6 (E)
/LCDBackPack/LCD_BL: R57.1; also elsewhere on the board
/LCDBackPack/LED1: R55.2, U11.6 (QG)
/LCDBackPack/LED2: R56.2, U11.7 (QH)
/LCDBackPack/RS: U11.15 (QA), U12.4 (RS)
/LCDBackPack/RST: U11.5 (QF), U12.17 (RST)
/LCDBackPack/RW: U11.1 (QB), U12.5 (R/W)
/LCDBackPack/SCLK: U10.11 (SRCLK), U11.11 (SRCLK); also elsewhere on the board
/LCDBackPack/SI: U10.14 (SER); also elsewhere on the board
GND: C13.2, C14.2, C15.2, C16.2, C17.2, D13.2 (K), D14.2 (K), Q19.1 (E), RV1.1, U10.8 (GND), U10.13 (G), U11.8 (GND), U11.13 (G), U12.2 (VDD); also elsewhere on the board
unnamed: D13.1 (A), R55.1
unnamed: RV1.2, U12.3 (VO)
unnamed: RV1.3, U12.18 (VEE)
unnamed: Q19.2 (B), R57.2
unnamed: C17.1, Q19.3 (C), U12.20 (V-)
unnamed: D14.1 (A), R56.1
unnamed: U10.9 (~QH), U11.14 (SER)

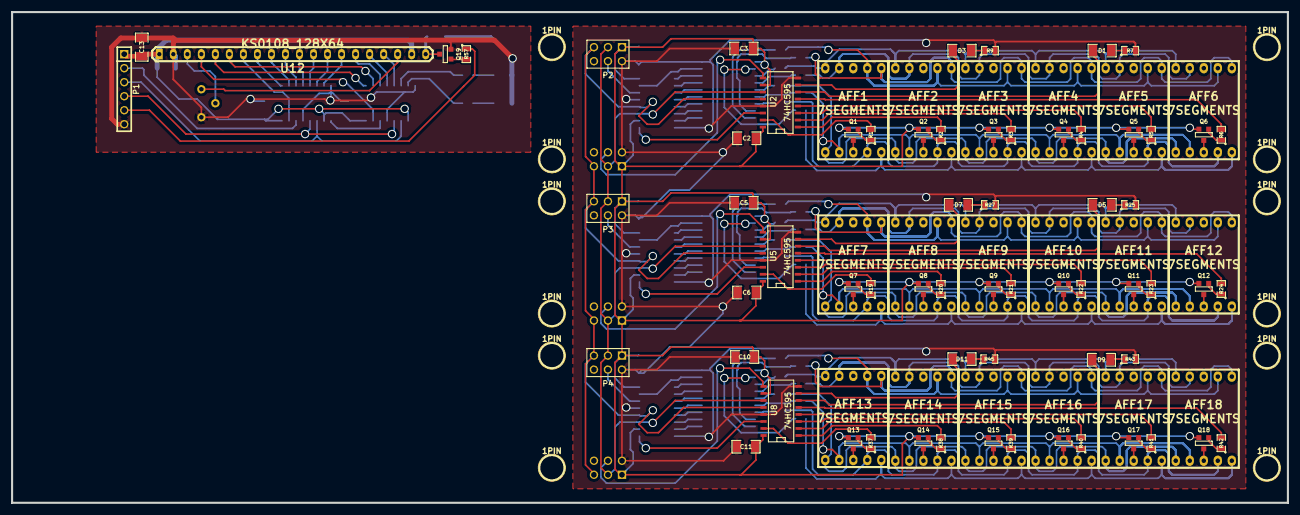
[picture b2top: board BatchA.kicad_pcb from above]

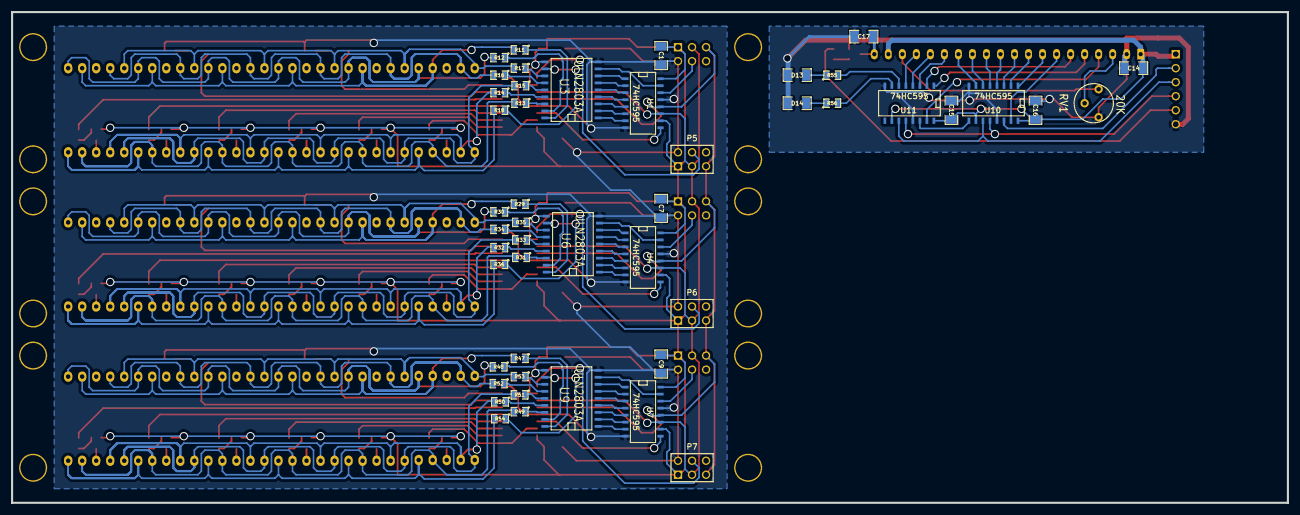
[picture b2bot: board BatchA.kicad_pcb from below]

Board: 2 copper layers, 231.1 x 88.9 mm, 142 parts (47 on the bottom side), 178 nets.

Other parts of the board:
1PIN, 1PIN#2, 1PIN#3, 1PIN#4, 1PIN#5, 1PIN#6, 1PIN#7, 1PIN#8, 1PIN#9, 1PIN#10, 1PIN#11, 1PIN#12: P***; 1pin

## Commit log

2015-04-26 :circus_tent: Added .gitattributes
2015-04-26 AC Monitor Rev1
2016-02-27 Batch E added
